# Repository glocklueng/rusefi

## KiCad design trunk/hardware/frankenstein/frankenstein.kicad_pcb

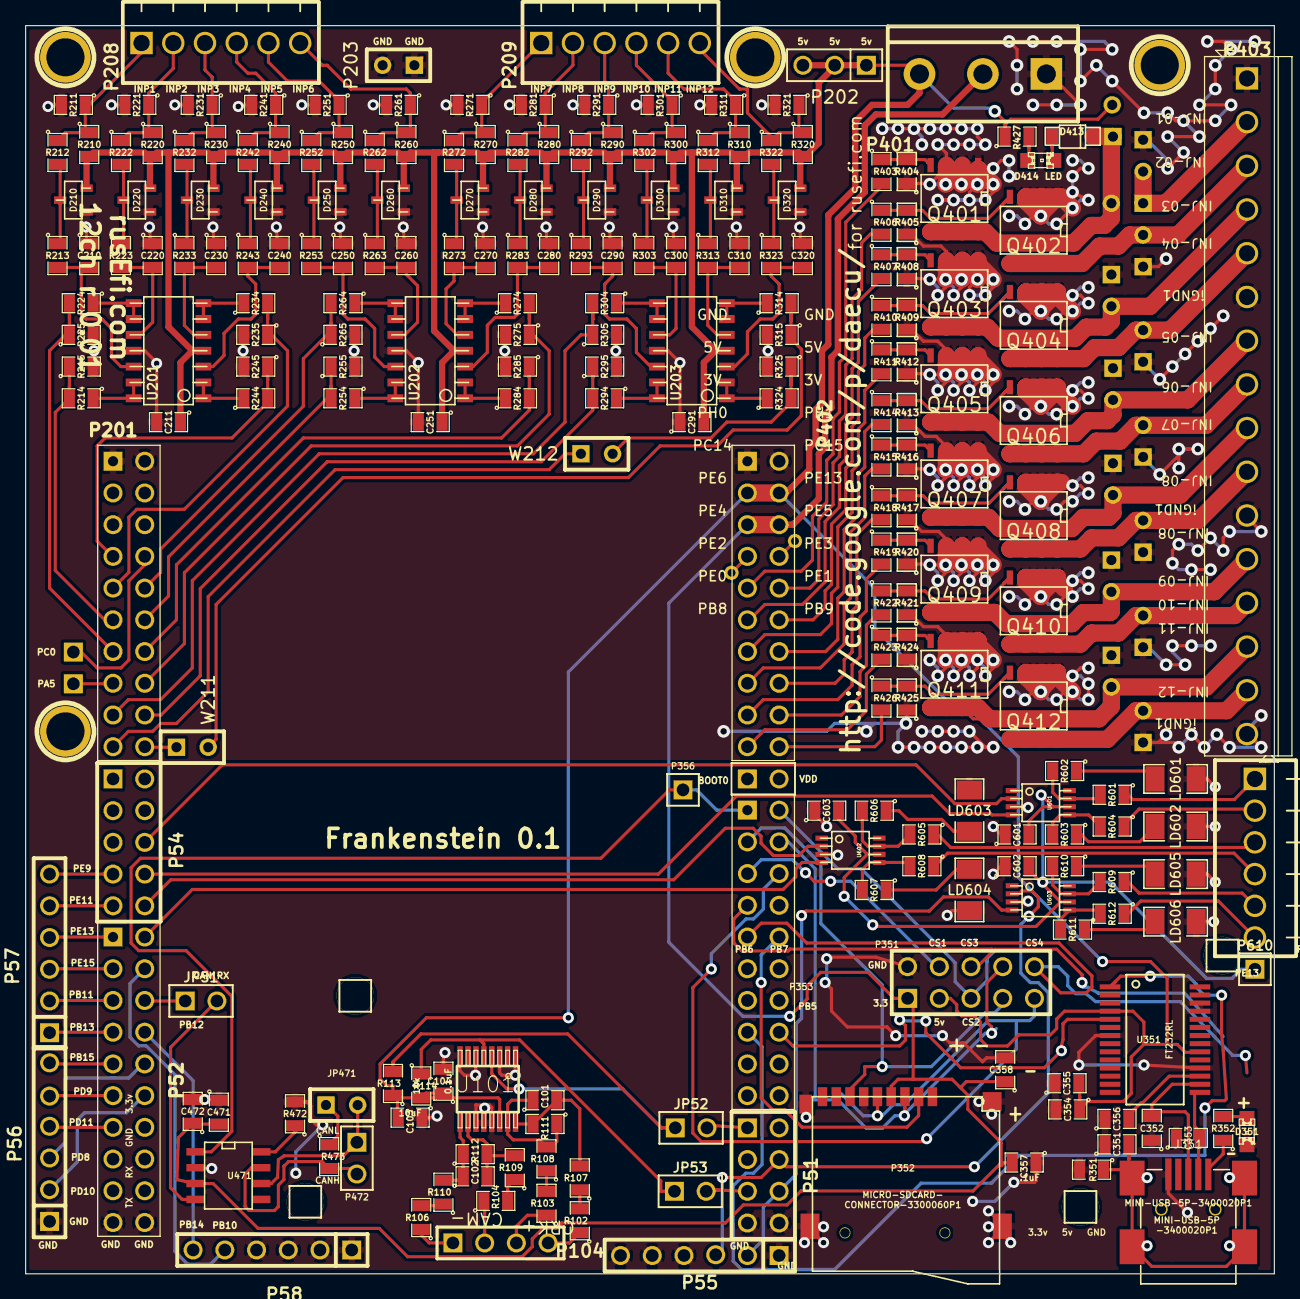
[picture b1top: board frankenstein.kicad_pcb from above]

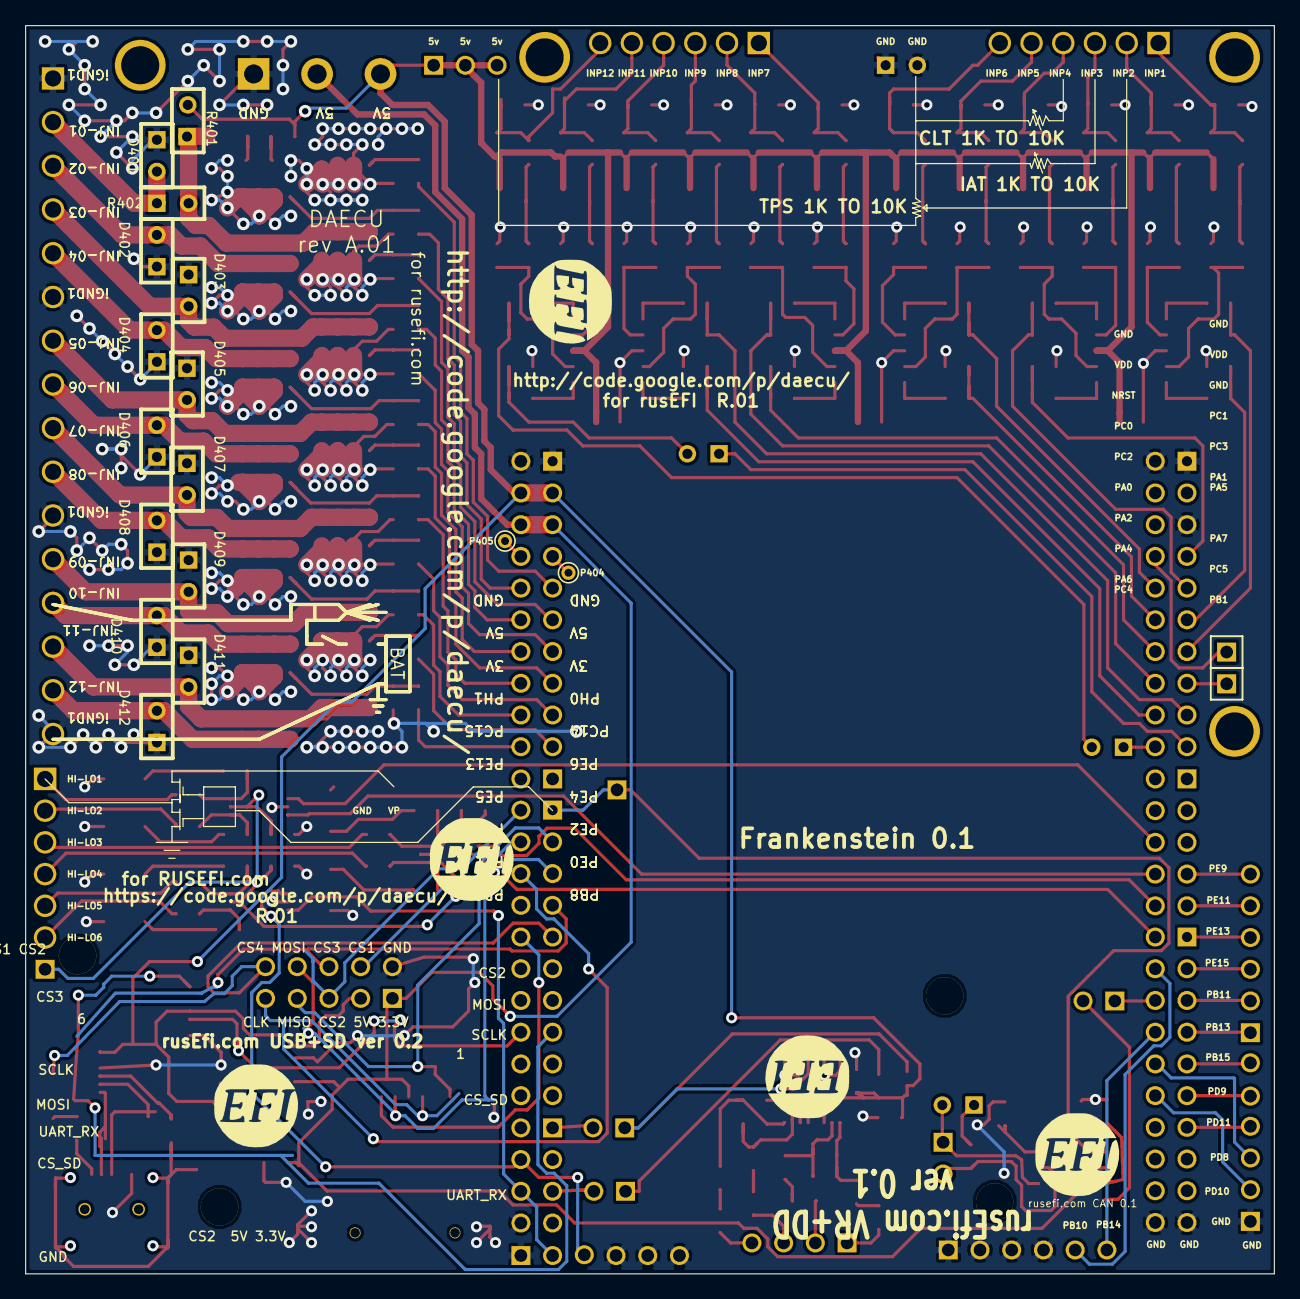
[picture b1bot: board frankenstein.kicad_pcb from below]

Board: 2 copper layers, 100.0 x 99.9 mm, 261 parts (23 on the bottom side), 185 nets.

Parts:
C101, C102: 1000pF; SM0805
C103: 10uF; SM0805
C104, C211, C251, C291, C601, C602, C603: 0.1uF; SM0805
C210, C220, C230, C240, C250, C260, C270, C280, C290, C300, C310, C320: 0.01uF; SM0805
C351: 4700pF; SM0805
C352, C353: 47pF; SM0805
C354, C358, C472: 4.7uF; SM0805
C355, C356, C357, C471: .1uF; SM0805
D210, D220, D230, D240, D250, D260, D270, D280, D290, D300, D310, D320: DOUBLE_SCHOTTKY; sot23
D351: GREEN; LED-0805
D401, D402, D403, D404, D405, D406, D407, D408, D409, D410, D411, D412: DIODE; SIL-2
D413: DIODE; SOD-123
D414: LED; LED-0805
G101, G201, G305, G471, G601: LOGO; LOGO_F
J351: MINI-USB-5P-3400020P1
JP51, JP52, JP53: JUMPER; PIN_ARRAY_2_A
JP471: JUMPER; SIL-2
LD601, LD602, LD603, LD604, LD605, LD606: LED; SM1206
M200, M201, M202, M401: CONN_1; 1pin
M351, M352, M470, M471: CONN_1; PIN_ARRAY_1
P51: CONN_4X2; pin_array_4x2
P52, P201: CONN_10X2; PIN_ARRAY_10X2_M
P53: CONN_2; PIN_ARRAY_2X1
P54, P351: CONN_5X2; PIN_ARRAY_5x2
P55, P56, P57, P58: CONN_6; PIN_ARRAY-6X1
P104: CONN_4; PIN_ARRAY_4x1
P202: CONN_3; PIN_ARRAY_3X1
P203: CONN_2; SIL-2
P204, P205, P356, P610: CONN_1; PIN_ARRAY_1
P208, P209: CONN_6; 6_screw_term_.1in
P352: MICRO-SDCARD-CONNECTOR-3300060P1
P353: CONN_10X2; PIN_ARRAY_10X2
P401: CONN_3; bornier3
P402: CONN_10X2; pin_array_10x2
P403: CONN_16; SIL-16_3.5MM
P404, P405: CONN_1; PINTST
P472: CONN_2; PIN_ARRAY_2_A
P603: CONN_6; OSTVN06A150
Q401, Q402, Q403, Q404, Q405, Q406, Q407, Q408, Q409, Q410, Q411, Q412: OVP_DRIVER; SO8E_ST
R102, R103, R104, R106, R107, R108, R109, R110, R111, R112: 5k; SM0805
R113, R114, R212, R222, R232, R242, R252, R262, R272, R282, R292, R302, R312, R322, R472: 10k; SM0805
R210, R220, R230, R240, R250, R260, R270, R280, R290, R300, R310, R320, R602, R603, R606, R607, R610, R611: 2700; SM0805
R211, R221, R231, R241, R251, R261, R271, R281, R291, R301, R311, R321: 500K; SM0805
R213, R223, R233, R243, R253, R263, R273, R283, R293, R303, R313, R323, R601, R604, R605, R608, R609, R612: 100; SM0805
R214, R215, R224, R225, R234, R235, R244, R245, R254, R255, R264, R265, R274, R275, R284, R285, R294, R295, R304, R305, R314, R315, R324, R325: 1500; SM0805
R351: 1M; SM0805
R352: 1k; SM0805
R401: OPT; SIL-2
R402: 0R; SIL-2
R403, R406, R407, R410, R411, R414, R415, R418, R419, R422, R423, R426: 20R; SM0805
R404, R405, R408, R409, R412, R413, R416, R417, R420, R421, R424, R425, R427: 1K; SM0805
R473: 120; SM0805
U101: MAX9926/9927; maxim-10-QSOP16
U201, U202, U203: LMV324IDR; so-14
U351: FT232RL; ssop-28
U471: SN65HVD230; SO8E
U601, U602, U603: TC4427AVOA; msoic-8
W211, W212: TEST; SIL-2

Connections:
/3.3V: C357.2, C358.1, C471.2, C472.1, P351.1, P352.4, P401.2, P402.5, P402.6, U471.3
/5V: C103.2, C104.1, C211.1, C251.1, C291.2, C354.1, C355.2, D210.3, D220.3, D230.3, D240.3, D250.3, D260.3, D270.3, D280.3, D290.3, D300.3, D310.3, D320.3, P202.1, P202.2, P202.3, P351.3, P401.3, P402.3, P402.4, R113.1, R114.2, R210.2, R220.2, R230.2, R240.2, R250.2, R260.2, R270.2, R280.2, R290.2, R300.2, R310.2, R320.2, R401.2, R427.1, U101.14, U201.4, U202.4, U203.4, U351.4, U351.20
/CAM: JP53.1, R114.1, U101.5
/CAM+: P104.1, R106.1
/CAM-: P104.2, R104.1
/CANH: P472.2, R473.2, U471.7
/CANL: JP471.2, P472.1, U471.6
/CAN_RX: JP51.2, U471.4
/CAN_TX: P353.1, P356.1, U471.1
/CRANK: JP52.1, R113.2, U101.4
/CRK2+: P104.4, R102.1
/CRK2-: P104.3, R103.1
/CS1: P351.4, P353.5
/CS2: P351.5, P353.2
/CS3: P351.6, P353.7
/CS4: P351.10, P353.9
/CS_SD_MODULE: P352.2, P353.10
/HL1: P603.1, R601.1
/HL2: P603.2, R604.1
/HL3: P603.3, R605.1
/HL4: P603.4, R608.1
/HL5: P603.5, R609.1
/HL6: P603.6, R612.1
/H_IN1: P54.8, U601.4
/H_IN2: P54.10, U602.2
/H_IN3: P54.6, U601.2
/H_IN4: P52.2, U602.4
/H_IN5: P51.6, P55.2, U603.4
/H_IN6: P51.4, P55.3, U603.2
/INJ-01: D413.2, Q401.2, R401.1, R402.2
/INJ-01_2: D401.2, P403.2, R402.1
/INJ-01_5V: P402.9, R403.2
/INJ-02: D402.2, P403.3, Q402.2
/INJ-02_5V: P402.10, R406.2
/INJ-03: D403.2, P403.4, Q403.2
/INJ-03_5V: P402.11, R407.2
/INJ-04: D404.2, P403.5, Q404.2
/INJ-04_5V: P402.12, R410.2
/INJ-05: D405.2, P403.7, Q405.2
/INJ-05_5V: P402.13, R411.2
/INJ-06: D406.2, P403.8, Q406.2
/INJ-06_5V: P402.14, R414.2
/INJ-07: D407.2, P403.9, Q407.2
/INJ-07_5V: P402.15, R415.2
/INJ-08: D408.2, P403.10, Q408.2
/INJ-08_5V: P402.16, R418.2
/INJ-09: D409.2, P403.12, Q409.2
/INJ-09_5V: P402.17, R419.2
/INJ-10: D410.2, P403.13, Q410.2
/INJ-10_5V: P402.18, R422.2
/INJ-11: D411.2, P403.14, Q411.2
/INJ-11_5V: P402.19, R423.2
/INJ-12: D412.2, P403.15, Q412.2
/INJ-12_5V: P402.20, R426.2
/INP1: P208.1, R210.1, R211.1, R212.1
/INP2: P208.2, R220.1, R221.1, R222.1
/INP3: P208.3, R230.1, R231.1, R232.1
/INP4: P208.4, R240.1, R241.1, R242.1
/INP5: P208.5, R250.1, R251.1, R252.1
/INP6: P208.6, R260.1, R261.1, R262.1
/INP7: P209.1, R270.1, R271.1, R272.1
/INP8: P209.2, R280.1, R281.1, R282.1
/INP9: P209.3, R290.1, R291.1, R292.1
/INP10: P209.4, R300.1, R301.1, R302.1
/INP11: P209.5, R310.1, R311.1, R312.1
/INP12: P209.6, R320.1, R321.1, R322.1
/OUT1: P201.11, R214.2, R215.1
/OUT2: P201.13, R224.2, R225.1
/OUT3: P201.9, R234.2, R235.1
/OUT4: P201.7, R244.2, R245.1
/OUT5: P201.12, R254.2, R255.1
/OUT6: P201.10, R264.2, R265.1
/OUT7: P201.16, R274.2, R275.1
/OUT8: P201.14, R284.2, R285.1
/OUT9: P201.18, R294.2, R295.1
/OUT10: P201.17, R304.2, R305.1
/OUT11: P201.20, W211.1
/OUT12: P201.19, W212.1
/PA5: P201.15, P204.1
/PA8: JP52.2, P51.1
/PB10: P52.4, P58.5
/PB11: P52.5, P57.2
/PB12: JP51.1, P52.6
/PB13: P52.7, P57.1
/PB14: P52.8, P58.6
/PB15: P52.9, P56.6
/PC0: P201.8, P205.1
/PC6: JP53.2, P51.5
/PD8: P52.10, P56.3
/PD9: P52.11, P56.5
/PD10: P52.12, P56.2
/PD11: P52.13, P56.4
/PE9: P54.7, P57.6
/PE11: P54.9, P57.5
/PE13: P52.1, P57.4
/PE15: P52.3, P57.3
/PH0: P402.7, P404.1
/PH1: P402.8, P405.1
/SPI_MISO: P351.7, P352.7, P353.3
/SPI_MOSI: P351.8, P352.3, P353.4
/SPI_SCK: P351.9, P352.5, P353.6
/USART_RX: P353.16, U351.5
/USART_TX: P353.15, U351.1
/VP: C601.2, C602.2, C603.2, P610.1, U601.6, U602.6, U603.6
F-000020: R102.2, R107.1
F-000021: R104.2, R109.1
F-000023: R106.2, R110.1
F-000024: R103.2, R108.1
F-000025: C101.1, R108.2, R111.1, U101.15
F-000026: C101.2, R107.2, R111.2, U101.16
F-000027: C102.1, R110.2, R112.1, U101.9
F-000028: C102.2, R109.2, R112.2, U101.10
F-000056: D280.2, R282.2, R283.1
F-000057: R214.1, U201.13, U201.14
F-000058: R224.1, U201.8, U201.9
F-000059: D270.2, R272.2, R273.1
F-000060: R244.1, U201.1, U201.2
F-000061: D300.2, R302.2, R303.1
F-000062: D290.2, R292.2, R293.1
F-000063: R304.1, U203.8, U203.9
F-000064: R294.1, U203.13, U203.14
F-000065: C290.2, R293.2, U203.12
F-000066: D250.2, R252.2, R253.1
F-000067: C300.2, R303.2, U203.10
F-000068: R314.1, U203.6, U203.7
F-000069: R324.1, U203.1, U203.2
F-000070: C310.2, R313.2, U203.5
F-000071: C320.2, R323.2, U203.3
F-000072: D320.2, R322.2, R323.1
F-000073: D260.2, R262.2, R263.1
F-000074: D310.2, R312.2, R313.1
F-000075: R324.2, R325.1, W212.2
F-000076: R314.2, R315.1, W211.2
F-000077: C250.2, R253.2, U202.12
F-000078: D210.2, R212.2, R213.1
F-000079: R254.1, U202.13, U202.14
F-000080: R274.1, U202.6, U202.7
F-000081: R264.1, U202.8, U202.9
F-000082: C240.2, R243.2, U201.3
F-000083: C230.2, R233.2, U201.5
F-000084: C270.2, R273.2, U202.5
F-000085: C280.2, R283.2, U202.3
F-000086: C220.2, R223.2, U201.10
F-000087: D220.2, R222.2, R223.1
F-000088: C210.2, R213.2, U201.12
F-000089: C260.2, R263.2, U202.10
F-000090: R284.1, U202.1, U202.2
F-000091: D240.2, R242.2, R243.1
F-000093: D230.2, R232.2, R233.1
F-000094: R234.1, U201.6, U201.7
F-0000107: J351.1, R352.1
F-0000108: C353.2, J351.2, U351.15
F-0000109: D351.1, R352.2
F-0000110: C351.2, J351.6, R351.1
F-0000112: C356.2, U351.17
F-0000115: C352.2, J351.3, U351.16
F-0000143: Q408.1, R417.2, R418.1
F-0000144: Q404.1, R409.2, R410.1
F-0000145: Q406.1, R413.2, R414.1
F-0000146: Q402.1, R405.2, R406.1
F-0000147: D414.1, R427.2
F-0000148: Q410.1, R421.2, R422.1
F-0000149: D413.1, D414.2
F-0000150: Q412.1, R425.2, R426.1
F-0000151: Q401.1, R403.1, R404.2
F-0000152: Q405.1, R411.1, R412.2
F-0000153: Q403.1, R407.1, R408.2
F-0000154: Q409.1, R419.1, R420.2
F-0000155: Q407.1, R415.1, R416.2
F-0000156: Q411.1, R423.1, R424.2
F-0000161: JP471.1, R473.1
F-0000162: R472.1, U471.8
F-0000176: R603.2, R604.2, U601.5
F-0000177: R607.2, R608.2, U602.5
F-0000178: LD603.1, R606.1
F-0000179: R605.2, R606.2, U602.7
F-0000180: LD601.1, R602.1
F-0000181: R601.2, R602.2, U601.7
F-0000182: LD604.1, R607.1
F-0000183: LD606.1, R611.1
F-0000184: R609.2, R610.2, U603.7
F-0000185: R611.2, R612.2, U603.5
F-0000186: LD605.1, R610.1
F-0000187: LD602.1, R603.1
GND: C103.1, C104.2, C210.1, C211.2, C220.1, C230.1, C240.1, C250.1, C251.2, C260.1, C270.1, C280.1, C290.1, C291.1, C300.1, C310.1, C320.1, C351.1, C352.1, C353.1, C354.2, C355.1, C356.1, C357.1, C358.2, C471.1, C472.2, C601.1, C602.1, C603.1, D210.1, D220.1, D230.1, D240.1, D250.1, D260.1, D270.1, D280.1, D290.1, D300.1, D310.1, D320.1, D351.2, D401.1, D402.1, D403.1, D404.1, D405.1, D406.1, D407.1, D408.1, D409.1, D410.1, D411.1, D412.1, J351.5, LD601.2, LD602.2, LD603.2, LD604.2, LD605.2, LD606.2, P51.7, P51.8, P52.19, P52.20, P55.1, P55.4, P55.5, P55.6, P56.1, P58.1, P58.2, P58.3, P58.4, P201.1, P201.2, P201.5, P203.1, P203.2, P351.2, P352.6, P352.G1, P352.G2, P352.G3, P352.G4, P401.1, P402.1, P402.2, P403.1, P403.6, P403.11, P403.16, Q401.3, Q402.3, Q403.3, Q404.3, Q405.3, Q406.3, Q407.3, Q408.3, Q409.3, Q410.3, Q411.3, Q412.3, R211.2, R215.2, R221.2, R225.2, R231.2, R235.2, R241.2, R245.2, R251.2, R255.2, R261.2, R265.2, R271.2, R275.2, R281.2, R285.2, R291.2, R295.2, R301.2, R305.2, R311.2, R315.2, R321.2, R325.2, R351.2, R404.1, R405.1, R408.1, R409.1, R412.1, R413.1, R416.1, R417.1, R420.1, R421.1, R424.1, R425.1, R472.2, U101.1, U101.3, U101.6, U101.8, U101.11, U101.12, U101.13, U201.11, U202.11, U203.11, U351.7, U351.18, U351.21, U351.25, U351.26, U471.2, U601.3, U602.3, U603.3

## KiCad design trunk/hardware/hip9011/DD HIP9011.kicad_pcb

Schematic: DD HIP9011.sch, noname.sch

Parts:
C1: 100u
C2, C3: 47n
C4: 10u
C5: 100n
C6, C7: 20pF
C8: 22n
D1: HIP9011
D2: LED
D3: DIODE
G1: LOGO
P1: KNOCK 1
P2: KNOCK 2
P3: 12V
P4: CONN_4X2
R1, R2, R6: 1M
R3, R4, R15, R16: 10k
R5: 10R
R7, R8: 68k
R9: 470R
R10, R11, R12, R13, R14: 1K
U1: 7805-SOT89
X1: QUARTZ

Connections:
/+5V: C5.1, D1.1 (Vdd), R5.2, R10.1, R11.1, R12.1, R13.1, R14.1
/+12V: C1.1, P3.2 (PM), U1.3
/CS: D1.8 (CS), P4.4, R11.2
/GND: C1.2, C4.2, C5.2, C6.2, C7.2, C8.2, D1.2 (GND), D2.2 (K), P1.1, P2.1, P3.1, P4.2, R1.2, R2.2, R16.2, U1.2; also elsewhere on the board
/INT/HLD: D1.7 (INT/HLD), R10.2; also elsewhere on the board
/INTOUT: D1.4 (INTOUT), R15.1
/OUT: R15.2, R16.1; also elsewhere on the board
/SCK: D1.13 (SCK), P4.9, R13.2
/SI: D1.12 (SI), P4.8, R14.2
/SO: D1.11 (SO), P4.7
/TEST: D1.14 (TEST), R12.2; also elsewhere on the board
unnamed: D2.1 (A), R9.1
unnamed: C4.1, R5.1, R9.2, U1.1
unnamed: C7.1, D1.9 (OSCIN), R6.2, X1.2
unnamed: C3.1, P2.2 (PM), R2.1
unnamed: C3.2, R4.1
unnamed: C6.1, D1.10 (OSCOUT), R6.1, X1.1
unnamed: C8.1, D1.3 (Vmid), D1.15 (CH1NI), D1.20 (CH0NI)
unnamed: D1.16 (CH1IN), R3.2, R8.2
unnamed: D1.17 (GH1FB), R8.1
unnamed: D1.18 (CH0FB), R7.1
unnamed: D1.19 (CH0IN), R4.2, R7.2
unnamed: C2.2, R3.1
unnamed: C2.1, P1.2 (PM), R1.1

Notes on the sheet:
DD HIP9011 ver 0.1 RusEfi.com

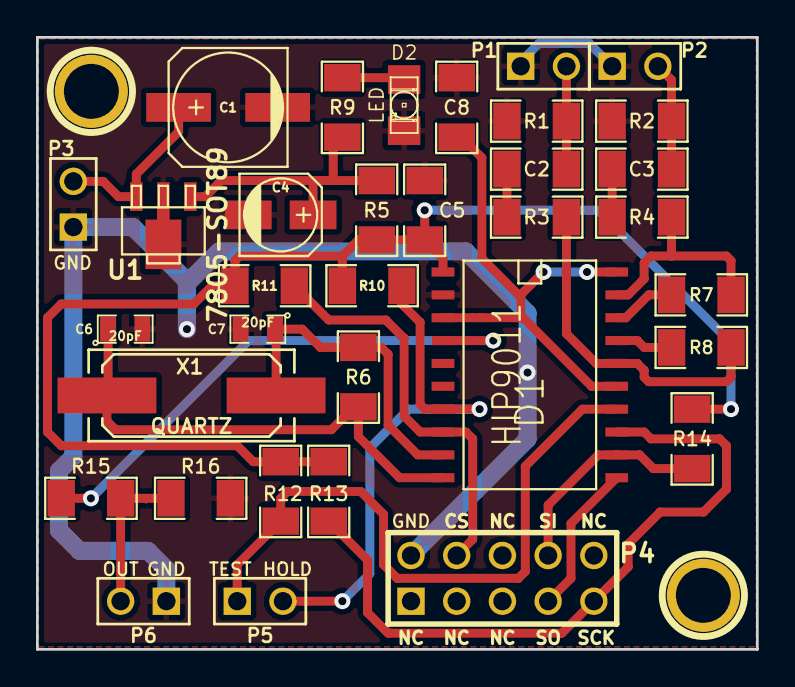
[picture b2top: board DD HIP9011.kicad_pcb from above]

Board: 2 copper layers, 40.0 x 34.0 mm, 35 parts (1 on the bottom side), 24 nets.

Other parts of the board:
P5, P6: CONN_2; PIN_ARRAY_2X1

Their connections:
/GND: P6.1; also elsewhere on the board
/INT/HLD: P5.2; also elsewhere on the board
/OUT: P6.2; also elsewhere on the board
/TEST: P5.1; also elsewhere on the board

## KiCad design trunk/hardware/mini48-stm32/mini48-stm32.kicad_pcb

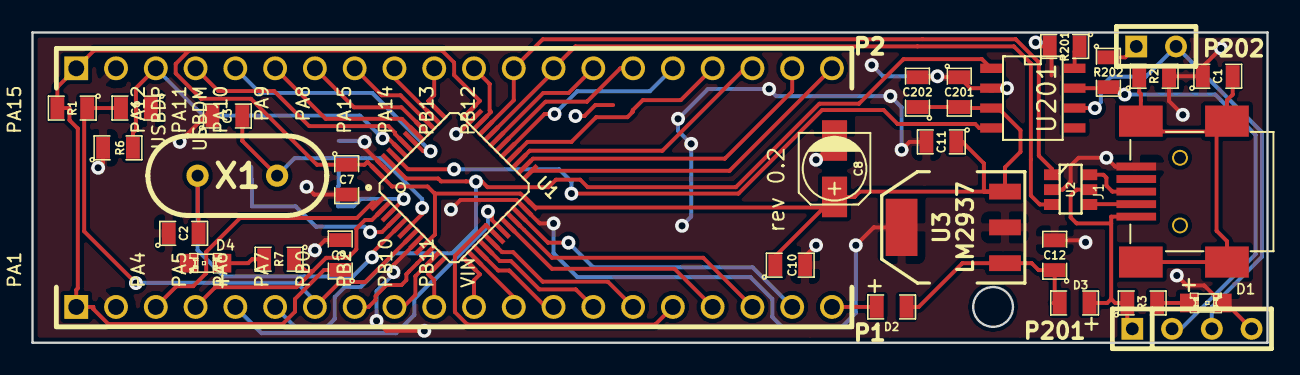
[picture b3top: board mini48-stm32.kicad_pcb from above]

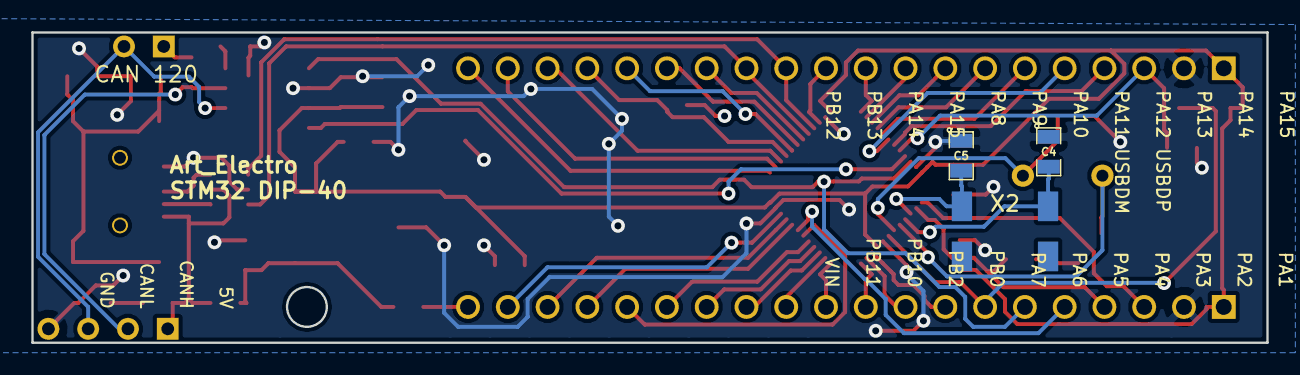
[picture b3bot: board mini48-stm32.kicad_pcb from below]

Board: 2 copper layers, 78.9 x 19.8 mm, 36 parts (3 on the bottom side), 54 nets.

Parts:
C1: 4700pF; SM0805
C2, C3, C4, C5: 18pF; SM0805
C6: 100nF; SM0805
C7, C10, C11: 1uF; SM0805
C8: 47uF; CP_elec_4x5.3
C9, C201: 0.1uF; SM0805
C12: 10uF; SM0805
C202: 4.7uF; SM0805
D1: GREEN; LED-0805_A
D2, D3: DIODESCH; SM0805-diode
D4: BLUE; LED-0805_A
J1: MINI-USB; MINI-USB-5P-3400020P1
P1, P2: CONN_20; PIN_ARRAY_20X1
P201: CONN_4; SIL-4
P202: JUMPER; JUMPER-2
R1, R3, R7: 1k; SM0805
R2: 1M; SM0805
R6, R201: 10k; SM0805
R202: 120; SM0805
U1: STM32F103C8; lqfp48
U2: NUF2101MT1G; SOT-457
U3: LM2937; SOT223
U201: SN65HVD230; SO8E
X1: 8MHz; HC-49V
X2: 32768KHz; MC-306

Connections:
/BOOT0: P2.3, R6.2, U1.44
/CAN BUS/3.3V: C7.1, C8.1, C9.1, C10.1, C11.1, C201.2, C202.1, P1.1, P2.1, R1.2, U1.9, U1.24, U1.36, U1.48, U3.3, U201.3
/CAN BUS/5V: D3.1, J1.1, P201.1, R3.1, U2.5
/CAN BUS/CANH: P201.2, R202.2, U201.7
/CAN BUS/CANL: P201.3, P202.2, U201.6
/CAN BUS/CAN_RX: U1.45, U201.4
/CAN BUS/CAN_TX: P1.6, U1.46, U201.1
/D+: J1.3, U2.6
/D-: J1.2, U2.4
/PA0: P1.8, U1.10
/PA1: P1.9, U1.11
/PA2: P1.10, U1.12
/PA3: P1.11, U1.13
/PA4: P1.12, U1.14
/PA5: P1.13, U1.15
/PA6: P1.14, U1.16
/PA7: P1.15, U1.17
/PA8: P2.16, U1.29
/PA9: P2.15, U1.30
/PA10: P2.14, U1.31
/PA11_USBDM: P2.13, U1.32, U2.3
/PA12_USBDP: P2.12, U1.33, U2.1
/PA13: P2.11, U1.34
/PA14: P2.10, U1.37
/PA15: P2.9, U1.38
/PB0: P1.16, U1.18
/PB1: P1.5, U1.19
/PB2: P1.17, U1.20
/PB3: P2.8, U1.39
/PB4: P2.7, U1.40
/PB5: P2.6, U1.41
/PB6: P2.5, U1.42
/PB7: P2.4, U1.43
/PB10: P1.18, U1.21
/PB11: P1.19, U1.22
/PB12: P2.20, U1.25
/PB13: P2.19, U1.26
/PB14: P2.18, U1.27
/PB15: P2.17, U1.28
/PC13: P1.4, R7.1, U1.2
/PC14_OSC32_IN: C5.2, U1.3, X2.2
/PC15_OSC32_OUT: C4.2, U1.4, X2.1
/PD0: C2.2, U1.5, X1.1
/PD1: C3.2, U1.6, X1.2
/Reset: C6.2, P1.7, R1.1, U1.7
/VBAT: P1.3, U1.1
/VIN: D2.1, P1.20
GND: C1.1, C2.1, C3.1, C4.1, C5.1, C6.1, C7.2, C8.2, C9.2, C10.2, C11.2, C12.2, C201.1, C202.2, D1.2, D4.2, J1.5, P1.2, P2.2, P201.4, R2.2, R6.1, R201.2, U1.8, U1.23, U1.35, U1.47, U2.2, U3.2, U3.4, U201.2
unnamed: C12.1, D2.2, D3.2, U3.1
unnamed: D4.1, R7.2
unnamed: D1.1, R3.2
unnamed: C1.2, J1.6, R2.1
unnamed: P202.1, R202.1
unnamed: R201.1, U201.8
